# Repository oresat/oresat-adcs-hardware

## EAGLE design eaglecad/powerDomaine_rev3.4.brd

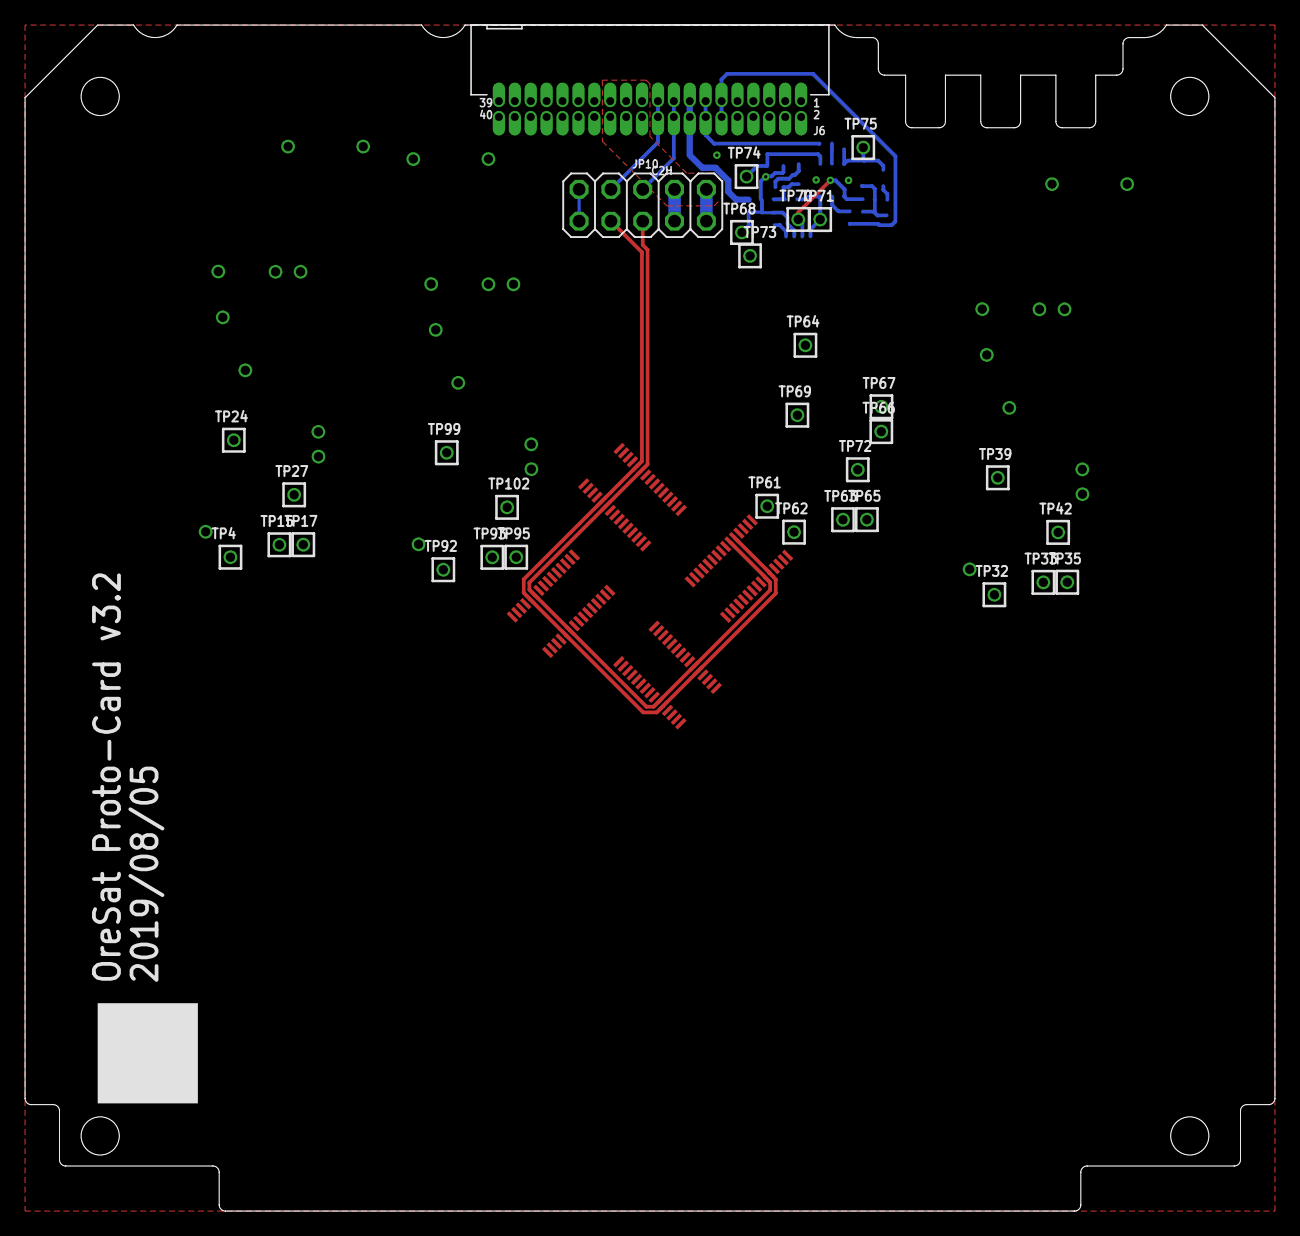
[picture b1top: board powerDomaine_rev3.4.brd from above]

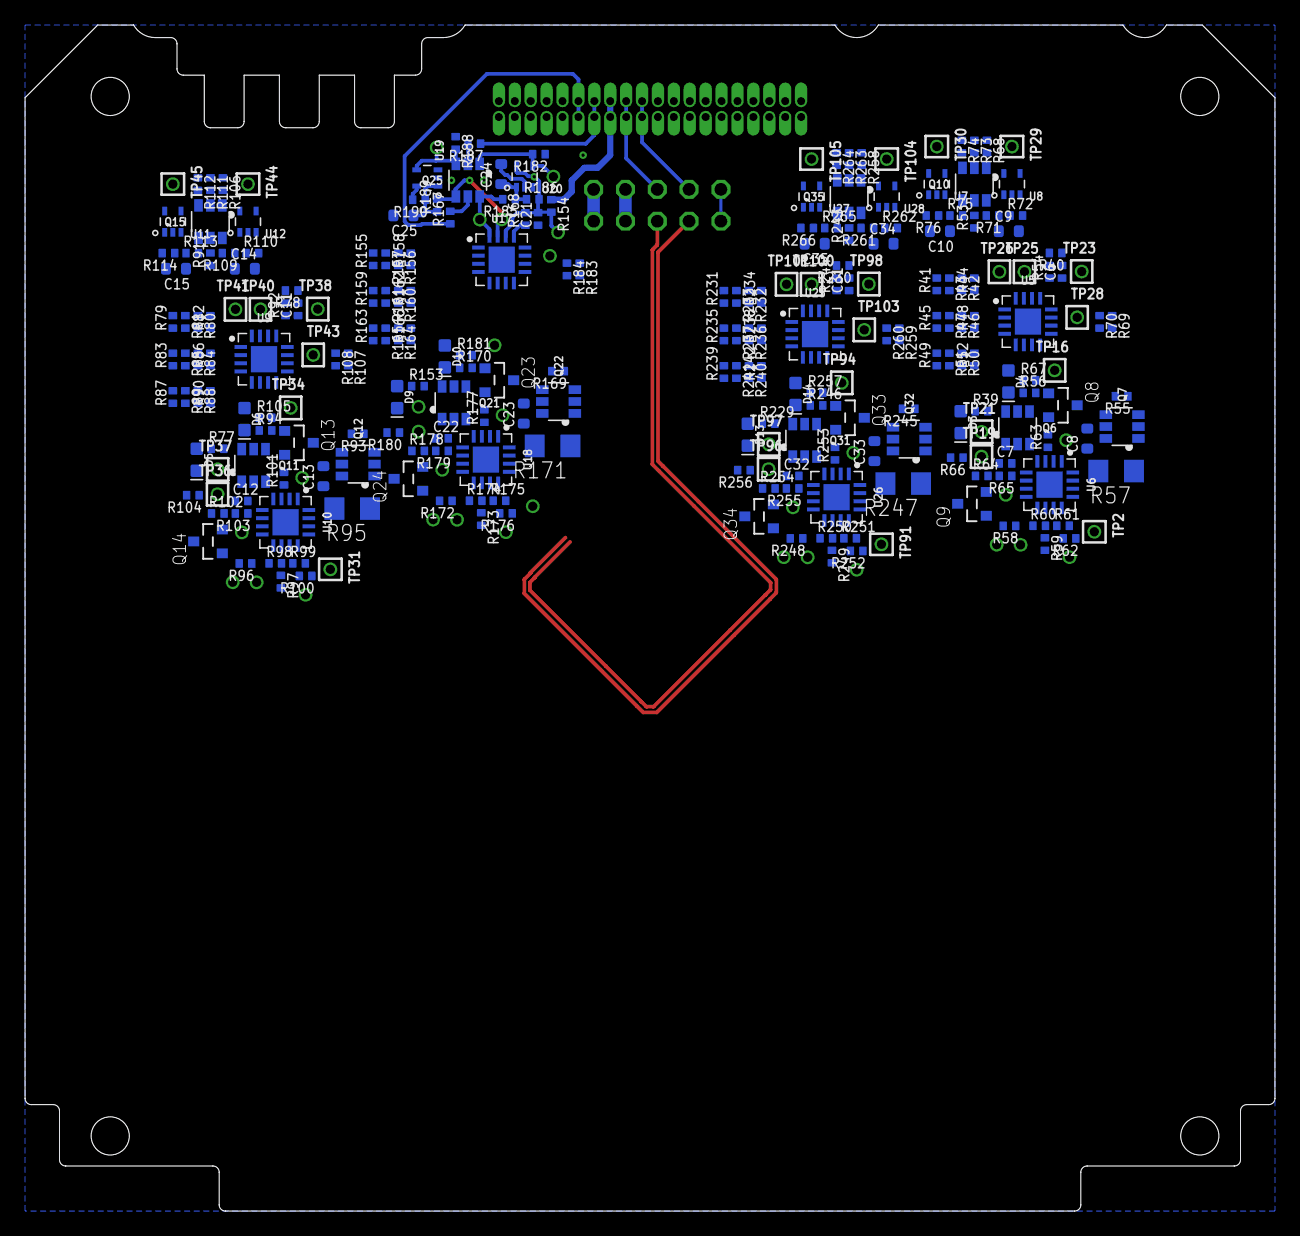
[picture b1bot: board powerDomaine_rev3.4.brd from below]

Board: 2 copper layers, 99.8 x 94.7 mm, 287 parts (246 on the bottom side), 155 nets.

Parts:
C6, C11, C21, C31: 100n; .0402-B-NOSILK
C7, C12, C22, C32: NP; .0402-B-NOSILK
C8, C9, C10, C13, C14, C15, C23, C24, C25, C33, C34, C35: 1u; .0603-B-NOSILK
D3, D5, D9, D13: GREEN; LED-0603
D4, D6, D10, D14: AMBER; LED-0603
H1, H2, H3, H4: STAND-OFFTIGHT; STAND-OFF-TIGHT
J6: J-SAMTEC-TFM-120-X1-XXX-D-RA
JP10: 2X05
Q6, Q7, Q11, Q12, Q21, Q22, Q31, Q32: MOSFET-PCH-SOT23-6; SOT23-6
Q8, Q9, Q13, Q14, Q23, Q24, Q33, Q34: PMV45EN; SOT23
Q10, Q15, Q25, Q35: DMP2240UDM; SOT23-6
R39, R67, R77, R105, R153, R181, R229, R257: 2.7k; .0402-B-NOSILK
R40, R53, R73, R78, R91, R111, R154, R167, R187, R230, R243, R263: 100; .0402-B-NOSILK
R41, R42, R43, R44, R45, R46, R47, R48, R49, R50, R51, R52, R60, R62, R64, R65, R79, R80, R81, R82, R83, R84, R85, R86, R87, R88, R89, R90, R98, R100, R102, R103, R155, R156, R157, R158, R159, R160, R161, R162, R163, R164, R165, R166, R174, R176, R178, R179, R231, R232, R233, R234, R235, R236, R237, R238, R239, R240, R241, R242, R250, R252, R254, R255: NP; .0402-B-NOSILK
R54, R55, R56, R58, R63, R66, R68, R74, R92, R93, R94, R96, R101, R104, R106, R112, R168, R169, R170, R172, R177, R180, R182, R188, R244, R245, R246, R248, R253, R256, R258, R264: 10k; .0402-B-NOSILK
R57, R95, R171, R247: 100m; R1206
R59, R61, R97, R99, R173, R175, R249, R251: 0; .0402-B-NOSILK
R69, R70, R107, R108, R183, R184, R259, R260: 47k; .0402-B-NOSILK
R71, R75, R109, R113, R185, R189, R261, R265: 330k; .0402-B-NOSILK
R72, R76, R110, R114, R186, R190, R262, R266: 1M; .0402-B-NOSILK
TP2, TP4, TP15, TP16, TP17, TP19, TP21, TP23, TP24, TP25, TP26, TP27, TP28, TP29, TP30, TP31, TP32, TP33, TP34, TP35, TP36, TP37, TP38, TP39, TP40, TP41, TP42, TP43, TP44, TP45, TP61, TP62, TP63, TP64, TP65, TP66, TP67, TP68, TP69, TP70, TP71, TP72, TP73, TP74, TP75, TP91, TP92, TP93, TP94, TP95, TP96, TP97, TP98, TP99, TP100, TP101, TP102, TP103, TP104, TP105: TEST-POINT; 2MM-TEST-POINT
U5, U9, U17, U25: MAX7310ATE; QFN65P400X400X80-17T210
U6, U10, U18, U26: MAX4211FETE; QFN65P400X400X80-17T210
U7, U8, U11, U12, U19, U20, U27, U28: MIC842LYC5; SC70-5
U$1, U$3, U$4, U$5: MEZZANINE_PLUG
U$2: ORESAT-CARD-V1.1-3XRF

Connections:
!FAULT_Q1: Q14.3, R104.1, TP36.1, U9.7
!FAULT_Q2: Q24.3, R180.1, TP66.1, U17.7
!FAULT_Q3: Q34.3, R256.1, TP96.1, U25.7
!FAULT_Q4: Q9.3, R66.1, TP19.1, U5.7
AD0_Q1: R79.1, R80.2, R81.2, R82.1, U9.1
AD0_Q2: R155.1, R156.2, R157.2, R158.1, U17.1
AD0_Q3: R231.1, R232.2, R233.2, R234.1, U25.1
AD0_Q4: R41.1, R42.2, R43.2, R44.1, U5.1
AD1_Q1: R83.1, R84.2, R85.2, R86.1, U9.2
AD1_Q2: R159.1, R160.2, R161.2, R162.1, U17.2
AD1_Q3: R235.1, R236.2, R237.2, R238.1, U25.2
AD1_Q4: R45.1, R46.2, R47.2, R48.1, U5.2
AD2_Q1: R87.1, R88.2, R89.2, R90.1, U9.3
AD2_Q2: R163.1, R164.2, R165.2, R166.1, U17.3
AD2_Q3: R239.1, R240.2, R241.2, R242.1, U25.3
AD2_Q4: R49.1, R50.2, R51.2, R52.1, U5.3
BOOT0_Q1: U9.10, U$1.P$9, U$1.P$22
BOOT0_Q2: U17.10, U$3.P$9, U$3.P$22
BOOT0_Q3: U25.10, U$4.P$9, U$4.P$22
BOOT0_Q4: U5.10, U$5.P$9, U$5.P$22
CAN2_H: J6.17, J6.18, JP10.5, JP10.6, U$1.P$6, U$1.P$25, U$3.P$6, U$3.P$25, U$4.P$6, U$4.P$25, U$5.P$6, U$5.P$25
CAN2_L: J6.19, J6.20, JP10.7, JP10.8, U$1.P$5, U$1.P$26, U$3.P$5, U$3.P$26, U$4.P$5, U$4.P$26, U$5.P$5, U$5.P$26
CB-RESET_Q1: R96.2, TP35.1, U9.9, U10.9
CB-RESET_Q2: R172.2, TP65.1, U17.9, U18.9
CB-RESET_Q3: R248.2, TP95.1, U25.9, U26.9
CB-RESET_Q4: R58.2, TP17.1, U5.9, U6.9
CB_CTRL_Q1: Q11.3, Q14.1, R101.1, TP42.1, U10.3, U10.4, U10.6
CB_CTRL_Q2: Q21.3, Q24.1, R177.1, TP72.1, U18.3, U18.4, U18.6
CB_CTRL_Q3: Q31.3, Q34.1, R253.1, TP102.1, U26.3, U26.4, U26.6
CB_CTRL_Q4: Q6.3, Q9.1, R63.1, TP27.1, U6.3, U6.4, U6.6
GND: C6.1, C8.2, C9.2, C10.2, C11.1, C13.2, C14.2, C15.2, C21.1, C23.2, C24.2, C25.2, C31.1, C33.2, C34.2, C35.2, D3.C, D4.C, D5.C, D6.C, D9.C, D10.C, D13.C, D14.C, J6.27, J6.28, J6.29, J6.30, J6.31, J6.32, J6.37, J6.38, JP10.9, JP10.10, Q8.2, Q9.2, Q13.2, Q14.2, Q23.2, Q24.2, Q33.2, Q34.2, R43.1, R47.1, R51.1, R56.1, R58.1, R60.1, R62.1, R64.1, R68.1, R74.1, R81.1, R85.1, R89.1, R94.1, R96.1, R98.1, R100.1, R102.1, R106.1, R112.1, R157.1, R161.1, R165.1, R170.1, R172.1, R174.1, R176.1, R178.1, R182.1, R188.1, R233.1, R237.1, R241.1, R246.1, R248.1, R250.1, R252.1, R254.1, R258.1, R264.1, U5.6, U5.EPAD, U6.7, U6.EPAD, U7.2, U8.2, U9.6, U9.EPAD, U10.7, U10.EPAD, U11.2, U12.2, U17.6, U17.EPAD, U18.7, U18.EPAD, U19.2, U20.2, U25.6, U25.EPAD, U26.7, U26.EPAD, U27.2, U28.2, U$1.P$1, U$1.P$2, U$1.P$14, U$1.P$15, U$1.P$16, U$1.P$17, U$1.P$29, U$1.P$30, U$3.P$1, U$3.P$2, U$3.P$14, U$3.P$15, U$3.P$16, U$3.P$17, U$3.P$29, U$3.P$30, U$4.P$1, U$4.P$2, U$4.P$14, U$4.P$15, U$4.P$16, U$4.P$17, U$4.P$29, U$4.P$30, U$5.P$1, U$5.P$2, U$5.P$14, U$5.P$15, U$5.P$16, U$5.P$17, U$5.P$29, U$5.P$30
IOUT_Q1: R97.2, U10.14
IOUT_Q2: R173.2, U18.14
IOUT_Q4: R59.2, U6.14
IOUT_Q_3: R249.2, U26.14
MAG1_Q1: U$1.P$10, U$1.P$21
MAG1_Q2: U$3.P$10, U$3.P$21
MAG1_Q3: U$4.P$10, U$4.P$21
MAG1_Q4: U$5.P$10, U$5.P$21
MAG2_Q1: U$1.P$11, U$1.P$20
MAG2_Q2: U$3.P$11, U$3.P$20
MAG2_Q3: U$4.P$11, U$4.P$20
MAG2_Q4: U$5.P$11, U$5.P$20
MAX4211-3V3_Q1: C13.1, TP39.1, U9.12, U10.1
MAX4211-3V3_Q2: C23.1, TP69.1, U17.12, U18.1
MAX4211-3V3_Q3: C33.1, TP99.1, U25.12, U26.1
MAX4211-3V3_Q4: C8.1, TP24.1, U5.12, U6.1
unnamed: D3.A, R39.1
unnamed: R54.1, U5.13
unnamed: Q7.3, Q8.3, R55.1
unnamed: Q7.1, Q7.2, Q7.5, Q7.6, R57.1, U6.16
unnamed: R59.1, R60.2, TP15.1, U6.10
unnamed: R61.1, R62.2, TP4.1, U6.11
unnamed: R61.2, U6.8, U6.12
unnamed: R65.1, U6.5
unnamed: C7.1, R64.2, R65.2
unnamed: Q6.4, R57.2, R63.2, U6.15
unnamed: D4.A, R67.1
unnamed: Q10.5, R53.2
unnamed: Q10.1, R68.2, TP29.1, U8.4
unnamed: R69.1, R70.1, TP28.1, U5.11
unnamed: Q10.2, R73.2
unnamed: Q10.3, R74.2, TP30.1, U7.4
unnamed: C10.1, R75.1, R76.1, U7.1
unnamed: C9.1, R71.1, R72.1, U8.1
unnamed: D5.A, R77.1
unnamed: R92.1, U9.13
unnamed: Q12.3, Q13.3, R93.1
unnamed: Q12.1, Q12.2, Q12.5, Q12.6, R95.1, U10.16
unnamed: R97.1, R98.2, TP33.1, U10.10
unnamed: R99.1, R100.2, TP32.1, U10.11
unnamed: R99.2, U10.8, U10.12
unnamed: R103.1, U10.5
unnamed: C12.1, R102.2, R103.2
unnamed: Q11.4, R95.2, R101.2, U10.15
unnamed: D6.A, R105.1
unnamed: Q15.5, R91.2
unnamed: Q15.1, R106.2, TP44.1, U12.4
unnamed: R107.1, R108.1, TP43.1, U9.11
unnamed: Q15.2, R111.2
unnamed: Q15.3, R112.2, TP45.1, U11.4
unnamed: C15.1, R113.1, R114.1, U11.1
unnamed: C14.1, R109.1, R110.1, U12.1
unnamed: D9.A, R153.1
unnamed: R168.1, U17.13
unnamed: Q22.3, Q23.3, R169.1
unnamed: Q22.1, Q22.2, Q22.5, Q22.6, R171.1, U18.16
unnamed: R173.1, R174.2, TP63.1, U18.10
unnamed: R175.1, R176.2, TP62.1, U18.11
unnamed: R175.2, U18.8, U18.12
unnamed: R179.1, U18.5
unnamed: C22.1, R178.2, R179.2
unnamed: Q21.4, R171.2, R177.2, U18.15
unnamed: D10.A, R181.1
unnamed: Q25.5, R167.2
unnamed: Q25.1, R182.2, TP74.1, U20.4
unnamed: R183.1, R184.1, TP73.1, U17.11
unnamed: Q25.2, R187.2
unnamed: Q25.3, R188.2, TP75.1, U19.4
unnamed: C25.1, R189.1, R190.1, U19.1
unnamed: C24.1, R185.1, R186.1, U20.1
unnamed: D13.A, R229.1
unnamed: R244.1, U25.13
unnamed: Q32.3, Q33.3, R245.1
unnamed: Q32.1, Q32.2, Q32.5, Q32.6, R247.1, U26.16
unnamed: R249.1, R250.2, TP93.1, U26.10
unnamed: R251.1, R252.2, TP92.1, U26.11
unnamed: R251.2, U26.8, U26.12
unnamed: R255.1, U26.5
unnamed: C32.1, R254.2, R255.2
unnamed: Q31.4, R247.2, R253.2, U26.15
unnamed: D14.A, R257.1
unnamed: Q35.5, R243.2
unnamed: Q35.1, R258.2, TP104.1, U28.4
unnamed: R259.1, R260.1, TP103.1, U25.11
unnamed: Q35.2, R263.2
unnamed: Q35.3, R264.2, TP105.1, U27.4
unnamed: C35.1, R265.1, R266.1, U27.1
unnamed: C34.1, R261.1, R262.1, U28.1
ON/!OFF_Q1: Q13.1, R94.2, R105.2, TP34.1, U9.8
ON/!OFF_Q2: Q23.1, R170.2, R181.2, TP64.1, U17.8
ON/!OFF_Q3: Q33.1, R246.2, R257.2, TP94.1, U25.8
ON/!OFF_Q4: Q8.1, R56.2, R67.2, TP16.1, U5.8
OPD_PWR: J6.15, J6.16, R40.1, R78.1, R154.1, R230.1
OPD_SCL: J6.13, J6.14, R73.1, R111.1, R187.1, R263.1
OPD_SDA: J6.11, J6.12, R53.1, R91.1, R167.1, R243.1
PB6/SCL_Q1: R108.2, U9.4, U$1.P$7, U$1.P$24
PB6/SCL_Q2: R184.2, U17.4, U$3.P$7, U$3.P$24
PB6/SCL_Q3: R260.2, U25.4, U$4.P$7, U$4.P$24
PB6/SCL_Q4: R70.2, U5.4, U$5.P$7, U$5.P$24
PB7/SDA_Q1: R107.2, U9.5, U$1.P$8, U$1.P$23
PB7/SDA_Q2: R183.2, U17.5, U$3.P$8, U$3.P$23
PB7/SDA_Q3: R259.2, U25.5, U$4.P$8, U$4.P$23
PB7/SDA_Q4: R69.2, U5.5, U$5.P$8, U$5.P$23
PEN-SCL-FILT_Q1: Q15.4, R80.1, R84.1, R88.1, R113.2, TP40.1, U9.15
PEN-SCL-FILT_Q2: Q25.4, R156.1, R160.1, R164.1, R189.2, TP70.1, U17.15
PEN-SCL-FILT_Q3: Q35.4, R232.1, R236.1, R240.1, R265.2, TP100.1, U25.15
PEN-SCL-FILT_Q4: Q10.4, R42.1, R46.1, R50.1, R75.2, TP25.1, U5.15
PEN-SDA-FILT_Q1: Q15.6, R82.2, R86.2, R90.2, R109.2, TP41.1, U9.16
PEN-SDA-FILT_Q2: Q25.6, R158.2, R162.2, R166.2, R185.2, TP71.1, U17.16
PEN-SDA-FILT_Q3: Q35.6, R234.2, R238.2, R242.2, R261.2, TP101.1, U25.16
PEN-SDA-FILT_Q4: Q10.6, R44.2, R48.2, R52.2, R71.2, TP26.1, U5.16
POUT_Q1: TP31.1, U10.13
POUT_Q2: TP61.1, U18.13
POUT_Q3: TP91.1, U26.13
POUT_Q4: TP2.1, U6.13
VBUS: J6.21, J6.22, J6.23, J6.24, J6.25, J6.26, JP10.1, JP10.2, JP10.3, JP10.4, Q7.4, Q12.4, Q22.4, Q32.4, R55.2, R93.2, R169.2, R245.2
VBUSP_Q1: C12.2, Q11.1, Q11.2, Q11.5, Q11.6, R77.2, TP37.1, U$1.P$3, U$1.P$4, U$1.P$12, U$1.P$13, U$1.P$18, U$1.P$19, U$1.P$27, U$1.P$28
VBUSP_Q2: C22.2, Q21.1, Q21.2, Q21.5, Q21.6, R153.2, TP67.1, U$3.P$3, U$3.P$4, U$3.P$12, U$3.P$13, U$3.P$18, U$3.P$19, U$3.P$27, U$3.P$28
VBUSP_Q3: C32.2, Q31.1, Q31.2, Q31.5, Q31.6, R229.2, TP97.1, U$4.P$3, U$4.P$4, U$4.P$12, U$4.P$13, U$4.P$18, U$4.P$19, U$4.P$27, U$4.P$28
VBUSP_Q4: C7.2, Q6.1, Q6.2, Q6.5, Q6.6, R39.2, TP21.1, U$5.P$3, U$5.P$4, U$5.P$12, U$5.P$13, U$5.P$18, U$5.P$19, U$5.P$27, U$5.P$28
VPD_Q1: C11.2, R78.2, R79.2, R83.2, R87.2, R92.2, R104.2, R110.2, R114.2, TP38.1, U9.14, U11.5, U12.5
VPD_Q2: C21.2, R154.2, R155.2, R159.2, R163.2, R168.2, R180.2, R186.2, R190.2, TP68.1, U17.14, U19.5, U20.5
VPD_Q3: C31.2, R230.2, R231.2, R235.2, R239.2, R244.2, R256.2, R262.2, R266.2, TP98.1, U25.14, U27.5, U28.5
VPD_Q4: C6.2, R40.2, R41.2, R45.2, R49.2, R54.2, R66.2, R72.2, R76.2, TP23.1, U5.14, U7.5, U8.5

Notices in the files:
parts and their libraries:
SparkFun-Hardware: Licensing: Creative Commons ShareAlike 4.0 International - https://creativecommons.org/licenses/by-sa/4.0
